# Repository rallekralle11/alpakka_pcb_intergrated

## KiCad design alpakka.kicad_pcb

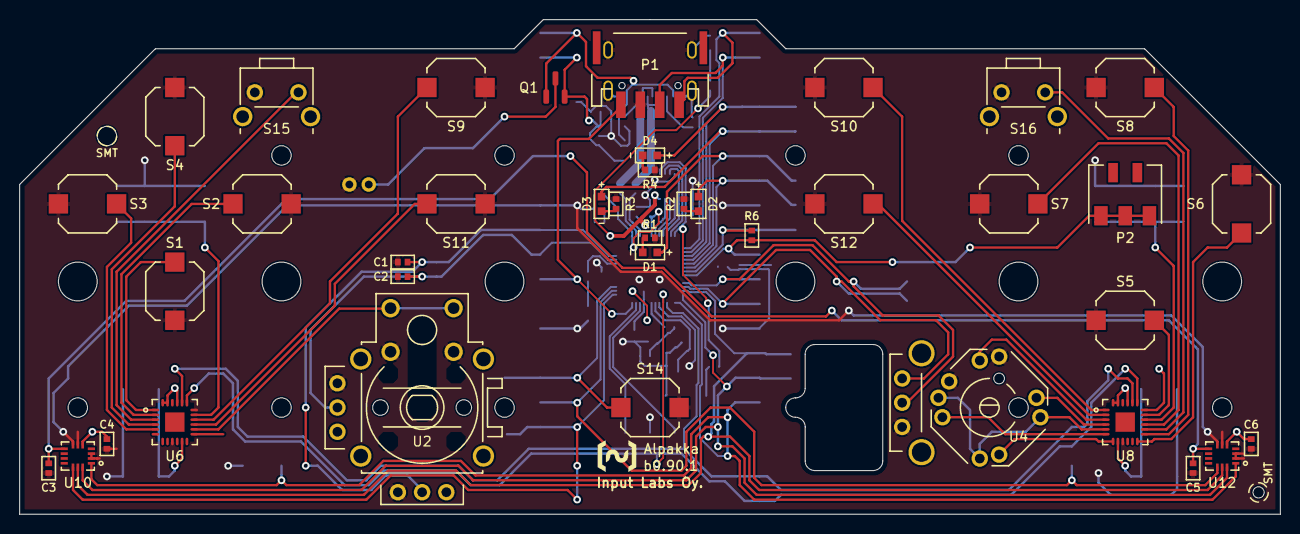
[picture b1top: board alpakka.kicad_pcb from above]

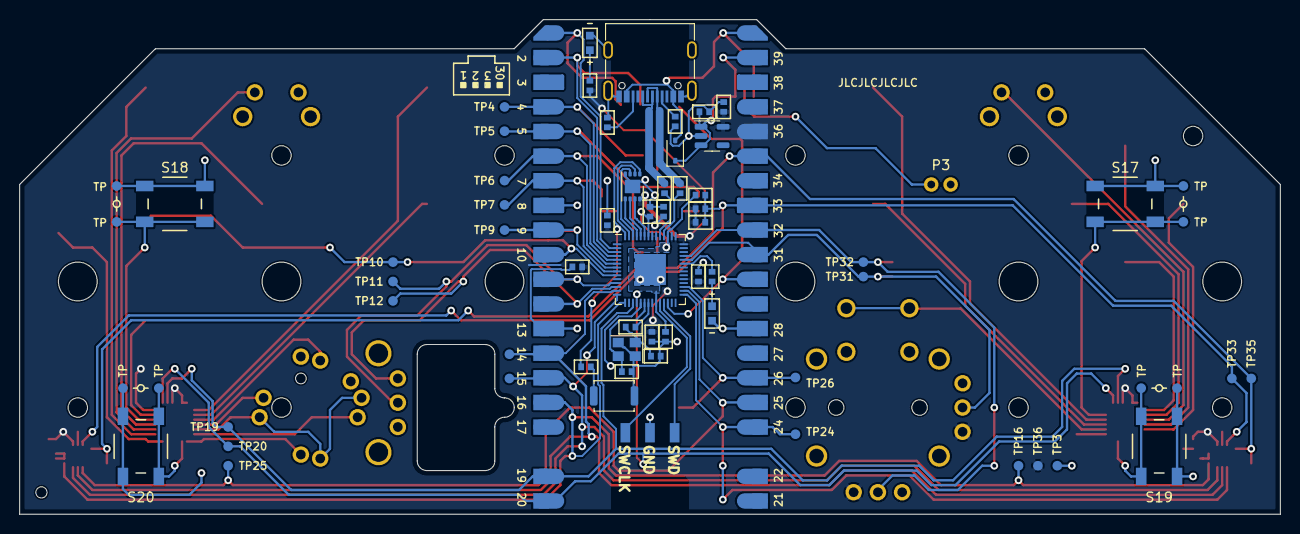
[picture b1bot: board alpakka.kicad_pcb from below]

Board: 2 copper layers, 130.0 x 51.0 mm, 108 parts (68 on the bottom side), 76 nets.

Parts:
C1, C2, C3, C4, C5, C6: C; 0402
C8, C9: TBD; 0402
C10, C11, C13, C14, C16, C17, C18, C20: 100nf; 0402
C12, C19: 2,2µf; 0402
C22: 1µf+; 0402
C23: 2,2µf+; 0402
D1, D2, D3, D4: Diode; 0603_d
D5: D_Small; D_SOD-323
D7: LED_GREEN; 0603_d
D9: LED_GREEN_PWR; 0603_d
J3: Debug; PinSocket_1x03_P2.54mm_Vertical
J4: USB_C_Receptacle_USB2.0; USB_C_Receptacle_G-Switch_GT-USB-7010ASV
P1: Debug; JST_S4B-PH-SM4-K-TB
P2: Endpoint; HRO_BC-25-3P
P3: Conn_01x02; JST_PH_2_TH
Q1: Q_PMOS_DGS; SOT-23-DGS
R1, R2, R3, R4: R; 0402
R6: R6; 0402
R8, R9: 27Ω; 0402
R10, R12: 1kΩ; 0402
R18, R20: 470Ω; 0402
R19, R22: 5,1kΩ; 0402
S1: down; Alpsalpine_SKPM
S2: right; Alpsalpine_SKPM
S3: left; Alpsalpine_SKPM
S4: up; Alpsalpine_SKPM
S5: a; Alpsalpine_SKPM
S6: b; Alpsalpine_SKPM
S7: x; Alpsalpine_SKPM
S8: y; Alpsalpine_SKPM
S9: select_1; Alpsalpine_SKPM
S10: start_1; Alpsalpine_SKPM
S11: select_2; Alpsalpine_SKPM
S12: start_2; Alpsalpine_SKPM
S14: home; Alpsalpine_SKPM
S15: l1; Alpsalpine_SKHHL
S16: r1; Alpsalpine_SKHHL
S17: l2; Alpsalpine_SKQG
S18: r2; Alpsalpine_SKQG
S19: l4; Alpsalpine_SKQG
S20: r4; Alpsalpine_SKQG
SW1: SW_MEC_5G; SW_Push_SPST_NO_Alps_SKRK
TP3, TP4, TP5, TP6, TP7, TP9, TP10, TP11, TP12, TP14, TP15, TP16, TP19, TP20, TP24, TP25, TP26, TP31, TP32, TP33, TP35, TP36, TP101, TP102, TP103, TP104, TP201, TP202, TP203, TP204: Endpoint; Pad_1mm
U1: Raspberry_Pico
U2: Alpsalpine_RKJXV; Alpsalpine_RKJXV122400R
U3: Alpsalpine_EC10E
U4: Alpsalpine_RKJXM; Alpsalpine_RKJXM1015004
U5: RP2040; QFN-56-1EP_7x7mm_P0.4mm_EP3.2x3.2mm
U6, U8: NXP_PCAL6416A; QFN24
U7: W25Q16JVUXIQ; SON-8-1EP_3x2mm_P0.5mm_EP1.4x1.6mm
U10, U12: ST_LSM6; LGA14
U11: LP2985-3.3; SOT-23-5
Y1: Crystal_16Mhz; Crystal_SMD_2520-4Pin_2.5x2.0mm

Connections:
+1V1: C10.2, C11.2, C12.2, U5.23 (DVDD), U5.45 (VREG_VOUT), U5.50 (DVDD)
A0: S1.2, U6.1 (P0)
A1: S2.2, U6.2 (P1)
A2: S15.2, U6.3 (P2)
A3: S4.2, U6.4 (P3)
A4: S3.2, U6.5 (P4)
A9: S19.2, TP204.1, U6.11 (P9)
A12: U2.8 (B), U2.10 (D), U6.14 (P12)
A13: S11.2, U6.15 (P13)
A14: S9.2, U6.16 (P14)
A15: S17.2, TP202.1, U6.17 (P15)
ADC0: C2.2, TP31.1, U1.31 (ADC_0), U2.2 (ADC0), U5.38 (GPIO26_ADC0)
ADC1: C1.2, TP32.1, U1.32 (ADC_1), U2.5 (ADC1), U5.39 (GPIO27_ADC1)
B0: S10.2, U8.1 (P0)
B1: S12.2, U8.2 (P1)
B2: U4.3 (C), U8.3 (P2)
B3: U4.2 (B), U8.4 (P3)
B4: U4.5 (PUSH), U8.5 (P4)
B5: U4.4 (D), U8.6 (P5)
B6: U4.1 (A), U8.7 (P6)
B7: S20.2, TP104.1, U8.8 (P7)
B10: S6.2, U8.12 (P10)
B11: S8.2, U8.13 (P11)
B12: S16.2, U8.14 (P12)
B13: S7.2, U8.15 (P13)
B14: S18.2, TP102.1, U8.16 (P14)
B15: S5.2, U8.17 (P15)
BAT: P3.1, Q1.1 (D)
CS0: TP24.1, U1.24 (GP_18), U5.29 (GPIO18), U10.12 (CS)
CS1: TP25.1, U1.25 (GP_19), U5.30 (GPIO19), U12.12 (CS)
D+: J4.A6 (D+), J4.B6 (D+), R8.2
D-: J4.A7 (D-), J4.B7 (D-), R9.1
DN: R9.2, U5.46 (USB_DM)
DP: R8.1, U5.47 (USB_DP)
GND: C1.1, C2.1, C3.1, C4.1, C5.1, C6.1, C8.1, C9.1, C10.1, C11.1, C12.1, C13.1, C14.1, C16.1, C17.2, C18.2, C19.2, C20.2, C22.1, C23.2, D7.1 (K), D9.1 (K), J3.2, J4.A1 (GND), J4.A12 (GND), J4.B1 (GND), J4.B12 (GND), J4.S1 (SHIELD), P1.3 (GND), P3.2, R1.1, R2.1, R3.1, R4.1, R19.2, R22.1, S1.1, S2.1, S3.1, S4.1, S5.1, S6.1, S7.1, S8.1, S9.1, S10.1, S11.1, S12.1, S14.1, S15.1, S16.1, S17.1, S18.1, S19.1, S20.1, SW1.1 (A), SW1.2 (A), TP3.1, TP33.1, TP101.1, TP103.1, TP201.1, TP203.1, U1.8 (GND), U1.13 (GND), U1.28 (GND), U1.33 (GND), U2.1 (GND0), U2.4 (GND1), U2.7 (A), U2.9 (C), U3.3 (GND), U4.6 (COM), U4.7 (GND), U5.19 (TESTEN), U5.57 (GND), U6.9 (VSS), U6.18 (ADDR), U7.4 (GND), U8.9 (VSS), U10.2 (SDx), U10.3 (SCx), U10.6 (GNDIO), U10.7 (GND), U11.2 (GND), U12.2 (SDx), U12.3 (SCx), U12.6 (GNDIO), U12.7 (GND), Y1.2, Y1.4
GP2: D4.2 (A), TP4.1, U1.4 (GP_2), U5.4 (GPIO2)
GP3: D3.2 (A), TP5.1, U1.5 (GP_3), U5.5 (GPIO3)
GP4: D1.2 (A), TP6.1, U1.6 (GP_4), U5.6 (GPIO4)
GP5: D2.2 (A), TP7.1, U1.7 (GP_5), U5.7 (GPIO5)
GP6: R6.1, TP9.1, U1.9 (GP_6), U5.8 (GPIO6)
GP7: P2.1, R6.2, TP10.1, U1.10 (GP_7), U5.9 (GPIO7)
GP8: TP11.1, U1.11 (GP_8), U3.2 (B), U5.11 (GPIO8)
GP9: TP12.1, U1.12 (GP_9), U3.1 (A), U5.12 (GPIO9)
GP20: S14.2, TP26.1, U1.26 (GP_20), U5.31 (GPIO20)
GP25: R20.1, U5.37 (GPIO25)
I2C_SCL: TP20.1, U1.20 (GP_15), U5.18 (GPIO15), U6.19 (SCL), U8.19 (SCL)
I2C_SDA: TP19.1, U1.19 (GP_14), U5.17 (GPIO14), U6.20 (SDA), U8.20 (SDA)
unnamed: C9.2, R10.2, Y1.1
unnamed: D1.1 (K), R1.2
unnamed: D2.1 (K), R2.2
unnamed: D3.1 (K), R3.2
unnamed: D4.1 (K), R4.2
unnamed: D7.2 (A), R20.2
unnamed: D9.2 (A), R18.2
unnamed: J4.A5 (CC1), R22.2
unnamed: J4.B5 (CC2), R19.1
unnamed: C8.2, U5.20 (XIN), Y1.3
unnamed: R10.1, U5.21 (XOUT)
QSPI_SCLK: U5.52 (QSPI_SCLK), U7.6 (CLK)
QSPI_SD0: U5.53 (QSPI_SD0), U7.5 (DI(IO0))
QSPI_SD1: U5.55 (QSPI_SD1), U7.2 (DO(IO1))
QSPI_SD2: U5.54 (QSPI_SD2), U7.3 (IO2)
QSPI_SD3: U5.51 (QSPI_SD3), U7.7 (IO3)
QSPI_SS: R12.2, U5.56 (QSPI_SS), U7.1 (~CS)
RUN: P1.4 (RUN), U1.30 (RUN), U5.26 (RUN)
SPI_CK: TP14.1, U1.14 (GP_10), U5.13 (GPIO10), U10.13 (SCL), U12.13 (SCL)
SPI_RX: TP16.1, U1.16 (GP_12), U5.15 (GPIO12), U10.1 (SDO), U12.1 (SDO)
SPI_TX: TP15.1, U1.15 (GP_11), U5.14 (GPIO11), U10.14 (SDA), U12.14 (SDA)
SWCLK: J3.1, U5.24 (SWCLK)
SWD: J3.3, U5.25 (SWD)
UART_RX: P1.2 (UART_RX), U1.2 (GP_1), U5.3 (GPIO1)
UART_TX: P1.1 (UART_TX), U1.1 (GP_0), U5.2 (GPIO0)
VBUS: D5.2 (A), J4.A4 (VBUS), J4.A9 (VBUS), J4.B4 (VBUS), J4.B9 (VBUS), Q1.2 (G), U1.40 (VBUS)
VCC: C4.2, C6.2, C13.2, C14.2, C16.2, C17.1, C18.1, C19.1, C20.1, C23.1, R18.1, TP36.1, U1.36 (3V3_OUT), U2.3 (VCC0), U2.6 (VCC1), U5.1 (IOVDD), U5.10 (IOVDD), U5.22 (IOVDD), U5.33 (IOVDD), U5.42 (IOVDD), U5.43 (ADC_AVDD), U5.44 (VREG_IN), U5.48 (USB_VDD), U5.49 (IOVDD), U6.21 (VDD), U6.23 (VDDBUS), U6.24 (RESET), U7.8 (VCC), U8.18 (ADDR), U8.21 (VDD), U8.23 (VDDBUS), U8.24 (RESET), U10.5 (VDDIO), U11.5 (VOUT), U12.5 (VDDIO)
VCCA: C3.2, C5.2, TP35.1, U1.35 (ADC_VREF), U10.8 (VDD), U12.8 (VDD)
VSYS: C22.2, D5.1 (K), Q1.3 (S), U1.39 (VSYS), U11.1 (VIN), U11.3 (ON/~OFF)

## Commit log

2023-12-22 components added, not wired
2024-01-07 finished routing
2024-01-07 and a bit more
2024-01-07 more edge clearance
2024-01-07 changed crystal to a more common size
2024-08-14 stuff
